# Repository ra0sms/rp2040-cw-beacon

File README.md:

# Beacon — CW (Morse) Beacon for HF or VHF Radio

A Morse-code beacon controller built around the [Waveshare RP2040-Zero](https://www.waveshare.com/wiki/RP2040-Zero) module (Raspberry Pi RP2040), designed for keying an HF/VHF FM/SSB/CW transmitter.

The project consists of:

- **Firmware** — generates a sine audio tone, controls the transmitter PTT and CW key, transmits a configurable message stored in flash and repeats it with a configurable pause. All parameters are configurable at runtime over a USB serial console and persist across power cycles.
- **Controller board** (KiCad) — power supply 8–15 V, audio output with attenuator and low-pass filter, open-collector PTT and CW key outputs, supply voltage divider and expansion headers. Gerber files are ready for ordering.
- **Desktop GUI** — configuration and monitoring tool for Linux and Windows.

## Repository layout

| Path | Contents |
|------|----------|
| [`code/Beacon/`](code/Beacon/) | Firmware source (Pico SDK, CMake) |
| [`firmware/`](firmware/) | Prebuilt firmware `.uf2` |
| [`gui/`](gui/) | Configuration GUI (`beacon_gui.py`, Windows build in `beacon_gui.zip`) |
| [`KiCad/beacon_rp2040/`](KiCad/beacon_rp2040/) | Board schematic and PCB (KiCad 10), schematic PDF, Gerber files, interactive BOM |
| [`scripts/`](scripts/) | Build / flash helper scripts |
| [`pics/`](pics/) | Schematic, 3D view, screenshots |

## Features

- **Telegraph tone output** — clean sine wave (DDS over a 62.5 kHz PWM carrier) with 5 ms raised-cosine rise/fall to avoid key clicks, 100–5000 Hz (600/800 Hz typical for FM audio), default **800 Hz**
- **PTT control** — asserted at the start of the transmission and released after the end of the message, with lead/tail delays
- **Morse message** — full A–Z, 0–9, `. , ? / - = @ : + ( ) " ' !` and prosigns (`<SK>`, `<BT>`, `<AR>`, …) encoding with standard element timing; speed set directly in WPM (default **20 WPM**)
- **Tone sequences** — an arbitrary chain of tone bursts ("freq:ms" pairs, `0` = silence), transmittable instead of (or after) the Morse message
- **Transmission modes** — `cw` (Morse only), `tones` (tone sequence only), or `both` (Morse, then tones) within one PTT
- **Non-volatile configuration** — stored in the last sector of the onboard flash; survives power-off and reflashing
- **Ready-to-flash firmware** — a prebuilt `.uf2` binary is included in [`firmware/`](firmware/), no toolchain required
- **USB console** — live configuration over the USB CDC serial port
- **Transmitter safety** — time-out timer (PTT is forcibly released after 120 s), hardware watchdog (reboot with PTT off if the firmware hangs), `txen 0` aborts the transmission immediately
- **Accurate keying** — the whole transmission is laid out in advance and played by a hardware timer, so console activity and USB output do not affect the timing
- **Status LED** — onboard WS2812 (GP16): steady green in the pause, red blinking in sync with the keying during transmission; brightness configurable

## Hardware

### Controller board

Two-layer board, 75 × 32 mm, four M3 mounting holes (connected to GND). The RP2040-Zero module is soldered flat onto the board by its castellated pads; its USB-C connector faces the board edge and is used for configuration and firmware updates. Full schematic: [`beacon_rp2040.pdf`](KiCad/beacon_rp2040/beacon_rp2040.pdf).

#### Main connector J1 (to the transmitter)

| Pin | Label | Function |
|-----|-------|----------|
| 1 | `8-15V` | Supply input, 8–15 V DC (reverse-polarity protected) |
| 2 | `GND` | Ground |
| 3 | `AUDIO` | Audio output → transmitter microphone / modulation input |
| 4 | `CW_OUT` | CW key output, open collector to GND (closed while the tone sounds) |
| 5 | `PTT_OUT` | PTT output, open collector to GND (closed during transmission) |
| 6 | `GND` | Ground |

#### Outputs

- **PTT / CW key** — BC817 NPN transistors, open collector to ground: connect directly to the radio's PTT and straight-key inputs (both are normally "close to ground" lines). Up to 45 V and ~50–100 mA. When switching a relay coil, put a flyback diode across the coil. Each output has a 100 nF capacitor to ground against RF pickup and a 10 kΩ pull-down on the base drive, so the outputs stay off while the module boots.
- **Audio** — GP15 sine → 34 kΩ / 1 kΩ divider → 47 nF low-pass (≈3.5 kHz, suppresses the 62.5 kHz PWM carrier) → 10 µF coupling capacitor. Output level is about 90 mV p-p (≈30 mV RMS) at the default settings — suitable for a microphone input. For a line/data input increase the 1 kΩ resistor (R2) or decrease the 34 kΩ resistor (R1).
- **Status LEDs** — headers `LED` / `CW`–`GND` and `LED` / `PTT`–`GND` for external indicator LEDs (anode to `CW`/`PTT`, cathode to `GND`; 1 kΩ series resistors are on the board). They light while the key is closed / PTT is active. The onboard WS2812 of the RP2040-Zero shows the beacon state as well.

#### Power supply

- Input 8–15 V → MBR0540 reverse-polarity diode → LM7805 (TO-220) → MBR0540 → +5 V rail → RP2040-Zero (its own 3.3 V regulator).
- The output diode isolates the regulator from USB: with only USB connected the board is powered from the computer (handy for configuration); with both connected the higher voltage wins, nothing is back-fed.
- The 7805 needs ~2 V of headroom plus ~0.3 V for the input diode, hence the 8 V minimum. At 13.8 V it dissipates about 8.5 V × load current — fine for the beacon itself (tens of mA) without a heatsink; keep external loads on the 5 V / 3.3 V headers small (≲100 mA) or add a heatsink.
- Supply voltage divider 100 kΩ / 10 kΩ + 100 nF to **GP26 (ADC0)**, ratio 1:11, range up to ~36 V — reserved for supply monitoring (not used by the firmware yet).

#### Expansion headers

| Header | Pins |
|--------|------|
| J2 `GPIOs` (18 pins) | 1 `3.3V`, 2–8 `GP0`–`GP6`, 9–14 `GP8`–`GP13`, 15–17 `GP27`–`GP29` (ADC1–ADC3), 18 `GND` |
| J3 `GND` | 3 × GND |
| J4 `5V` | 3 × +5 V rail (≈4.7 V after the isolation diode, or USB 5 V) |

GPIOs are 3.3 V logic and are not 5 V tolerant. GP7, GP14, GP15 and GP26 are used by the board and are not brought out.

#### RP2040-Zero pin usage

| Signal | GPIO | Description |
|--------|------|-------------|
| Tone   | GP15 | Audio tone (sine via PWM) → J1 `AUDIO` |
| PTT    | GP14 | PTT transistor → J1 `PTT_OUT`, PTT LED |
| CW key | GP7  | CW key transistor → J1 `CW_OUT`, CW LED |
| Vin sense | GP26 | Supply voltage divider (ADC0) |
| WS2812 | GP16 | Onboard status LED (built into the module) |

#### Manufacturing files

| File | Contents |
|------|----------|
| [`KiCad/beacon_rp2040/beacon_rp2040_gerbers.zip`](KiCad/beacon_rp2040/beacon_rp2040_gerbers.zip) | Gerber + drill files, ready to upload to a PCB manufacturer (2 layers, 1.6 mm) |
| [`KiCad/beacon_rp2040/gerbers/`](KiCad/beacon_rp2040/gerbers/) | The same files, unpacked |
| [`KiCad/beacon_rp2040/bom/ibom.html`](KiCad/beacon_rp2040/bom/ibom.html) | Interactive BOM / placement helper (download and open in a browser) |
| [`KiCad/beacon_rp2040/beacon_rp2040.pdf`](KiCad/beacon_rp2040/beacon_rp2040.pdf) | Schematic (PDF) |

#### Bill of materials

| Qty | Value | Package | References |
|-----|-------|---------|------------|
| 1 | Waveshare RP2040-Zero | castellated module | U1 |
| 1 | LM7805 | TO-220 | U2 |
| 2 | BC817 (2N7002 also fits) | SOT-23 | Q3, Q4 |
| 2 | MBR0540 | SOD-123 | D1, D4 |
| 1 | 34 kΩ (33 kΩ is fine) | 1206 | R1 |
| 1 | 100 kΩ | 1206 | R7 |
| 3 | 10 kΩ | 1206 | R3, R5, R8 |
| 5 | 1 kΩ | 1206 | R2, R4, R6, R9, R10 |
| 5 | 100 nF | 1206 | C2, C3, C5, C10, C11 |
| 3 | 10 µF ceramic, ≥25 V | 1206 | C4, C9, C12 |
| 1 | 47 nF | 1206 | C6 |
| 2 | 47 µF electrolytic, ≥25 V | radial 5 mm | C13, C14 |
| 1 | Pin header 1×6, 2.54 mm | THT | J1 |
| 1 | Pin header 1×18, 2.54 mm | THT | J2 |
| 2 | Pin header 1×3, 2.54 mm | THT | J3, J4 |
| 2 | Pin header 1×2, 2.54 mm (external LEDs) | THT | D2, D3 |

## Flashing

A prebuilt firmware binary is included in the repository: [`firmware/Beacon-v0.2.uf2`](firmware/Beacon-v0.2.uf2). You do not need to build anything to flash it.

**Method 1 — BOOTSEL button:**

1. Hold the BOOT button and connect the board via USB.
2. The board appears as a USB mass-storage device (`RPI-RP2`).
3. Copy the firmware: `cp firmware/Beacon-v0.2.uf2 /run/media/$USER/RPI-RP2/`

**Method 2 — picotool (no button required):**

```bash
picotool load firmware/Beacon-v0.2.uf2 -fx
```

If the currently running firmware does not support USB reboot, use the BOOTSEL button method.

## Configuration commands (USB console)

Connect to the board's serial port (`/dev/ttyACM0` on Linux, e.g. `minicom -D /dev/ttyACM0` or `picocom /dev/ttyACM0`). Any baud rate works.

Type the command and press **Enter**. If your terminal can send no line ending, the line is executed automatically after a 5-second pause in typing.

| Command        | Description                                        |
|----------------|----------------------------------------------------|
| `msg <text>`   | Set message text (A–Z, 0–9, `. , ? / - = @ : + ( ) " ' !`); prosigns in angle brackets are sent without letter gaps, e.g. `<SK>`, `<BT>`. Max 95 characters |
| `tone <hz>`    | Set tone frequency, 100–5000 Hz                    |
| `pause <sec>`  | Pause between message repeats, 0–3600 s            |
| `wpm <5..60>`  | Keying speed, words per minute (dot = 1200 / wpm)  |
| `tones <f:d> ...` | Tone sequence: `freq:ms` pairs, freq 0–5000 Hz (`0` = silence), duration 10–10000 ms, up to 24 entries. Without arguments — show current sequence |
| `txmode cw\|tones\|both` | What to transmit: Morse only / tone sequence only / both |
| `txen <0\|1>`   | Enable/disable transmission (0 = stops immediately, PTT released; beacon stays silent, e.g. while tuning) |
| `led <0..100>` | Status LED brightness, % (default 20)              |
| `save`         | Write current configuration to flash (during a transmission it is deferred until the transmission ends) |
| `show`         | Print current configuration                        |
| `default`      | Restore factory defaults                           |
| `ver`          | Firmware version (program version and git revision) |
| `help`         | Show command list                                  |

Changes take effect immediately (from the next transmission); use `save` to make them permanent. Invalid values are rejected with an `error:`/`usage:` reply and leave the setting unchanged. When the message, speed, mode or tone sequence makes a transmission longer than the 120 s time-out, a `warning:` is printed — such a transmission would be cut off. `show` also prints the transmission length (`txlen`).

The configuration is stored with a version number and CRC-32; a configuration saved by firmware v0.1 is migrated automatically on first boot.

### Example session

```
msg CQ CQ CQ DE RA0SMS K
tone 600
pause 15
wpm 18
txmode both
tones 800:150 0:100 800:150 0:100 1200:150 0:500
save
```

## Helper scripts

| Script | Purpose |
|--------|---------|
| [`scripts/build.sh`](scripts/build.sh) | Configure (once) and build the firmware → `code/Beacon/build/Beacon.uf2` |
| [`scripts/flash.sh`](scripts/flash.sh) | Flash the built firmware to the board via picotool (auto-detects the picotool from the Pico VS Code extension; override with `PICOTOOL=/path/to/picotool`) |
| [`scripts/build_gui_exe.bat`](scripts/build_gui_exe.bat) | (Windows) Build the standalone `gui/beacon_gui.exe` with PyInstaller (pack it into `gui/beacon_gui.zip` for the repository) |
| [`scripts/update_firmware.sh`](scripts/update_firmware.sh) | Copy the freshly built binary to the tracked [`firmware/Beacon-v0.2.uf2`](firmware/Beacon-v0.2.uf2) |

Typical workflow: `./scripts/build.sh && ./scripts/flash.sh`, then `./scripts/update_firmware.sh` before committing a new firmware version.

## Building from source

If you want to modify the firmware, build it yourself. The project uses:

- **[Raspberry Pi Pico SDK](https://github.com/raspberrypi/pico-sdk)** 2.3.1 (developed with this version; other 2.x versions likely work)
- **CMake** ≥ 3.13
- **ARM GCC cross-toolchain** — `arm-none-eabi-gcc` (the SDK 2.x toolchain package `15_2_Rel1` or any recent version)
- **Ninja** or GNU Make (Ninja is recommended)

### Installing the toolchain

**Fedora / RHEL:**

```bash
sudo dnf install arm-none-eabi-gcc-cs arm-none-eabi-newlib cmake ninja-build
git clone -b 2.3.1 https://github.com/raspberrypi/pico-sdk.git ~/pico-sdk
export PICO_SDK_PATH=~/pico-sdk   # add to ~/.bashrc or ~/.zshrc
```

**Debian / Ubuntu:**

```bash
sudo apt install gcc-arm-none-eabi libnewlib-arm-none-eabi libstdc++-arm-none-eabi-newlib cmake ninja-build
git clone -b 2.3.1 https://github.com/raspberrypi/pico-sdk.git ~/pico-sdk
export PICO_SDK_PATH=~/pico-sdk   # add to ~/.bashrc
```

Alternatively, install the official **Raspberry Pi Pico VS Code extension** — it manages the SDK, toolchain, ninja and picotool automatically (in `~/.pico-sdk`); the project's VS Code configuration in [`code/Beacon/.vscode/`](code/Beacon/.vscode/) is prepared for it.

### Building

```bash
cmake -B code/Beacon/build -S code/Beacon
cmake --build code/Beacon/build
```

The firmware binary is produced at `code/Beacon/build/Beacon.uf2`.

`picotool` (for USB flashing without the BOOTSEL button) is bundled with the VS Code extension, or can be built from [picotool](https://github.com/raspberrypi/picotool) / installed as `picotool` package on recent distros. Without it, use the BOOTSEL button method.

### Flashing the built firmware

**Method 1 — BOOTSEL button:**

1. Hold the BOOT button and connect the board via USB.
2. The board appears as a USB mass-storage device (`RPI-RP2`).
3. Copy the firmware: `cp code/Beacon/build/Beacon.uf2 /run/media/$USER/RPI-RP2/`

**Method 2 — picotool (no button required):**

```bash
picotool load code/Beacon/build/Beacon.uf2 -fx
```

If the currently running firmware does not support USB reboot, use the BOOTSEL button method.

## GUI (configuration tool)

A PyQt5/PyQt6 desktop GUI is available for convenient configuration and monitoring: [`gui/beacon_gui.py`](gui/beacon_gui.py).

**Windows users:** a standalone build that needs no Python installation is available: [`gui/beacon_gui.zip`](gui/beacon_gui.zip) — download, unpack and run `beacon_gui.exe`. On first launch the SmartScreen may warn about an unsigned binary; choose "More info" → "Run anyway".

Install the Python dependencies:

```bash
pip install -r requirements.txt
```

This installs **pyserial** and **PyQt5**. If only **PyQt6** is available (or PyQt5 is not installed), the GUI automatically uses PyQt6 instead — pyserial is required in either case.

Run the GUI:

```bash
python3 gui/beacon_gui.py
```

Features:

- Serial port selection with auto-detection of the Pico CDC port, connect/disconnect
- Editing all parameters: message, CW tone, keying speed (WPM), tone sequence, TX mode, pause, LED brightness; the message field only accepts characters the firmware can send
- **Apply** sends the fields one by one, waiting for the device's reply to each; rejected values and time-out warnings are reported in a summary dialog
- **Save to flash** — Apply, then `save`; **Read from device** — fills the fields from the device; **Defaults**
- **Transmission enabled** checkbox — temporarily stop the beacon (e.g. while tuning) and resume it later
- Firmware version display; a lost connection (cable unplugged, board reset) is detected automatically
- Live device log, optional hiding of TX monitor output
- Manual command line for any console command

On connection the GUI automatically requests the current configuration from the device and fills in the fields.

## Pin configuration

Pins and fixed parameters are defined at the top of [`code/Beacon/Beacon.c`](code/Beacon/Beacon.c):

```c
#define TONE_PIN          15   // Telegraph tone output
#define PTT_PIN           14   // PTT output (active high)
#define KEY_PIN           7    // CW key output (active high)
#define PTT_LEAD_MS       1000 // PTT lead-in delay, ms
#define PTT_TAIL_MS       100  // PTT tail delay, ms
#define TX_MAX_MS         120000 // Time-out timer: max PTT time per transmission, ms
#define WATCHDOG_MS       3000 // Watchdog timeout, ms
```

The PTT and CW key GPIOs are always **active high** (logic 1 while transmitting / keyed) — this is fixed in the firmware, no configuration needed. On the controller board they drive the open-collector transistors, so J1 `PTT_OUT` / `CW_OUT` are closed to ground while active.

## License

MIT

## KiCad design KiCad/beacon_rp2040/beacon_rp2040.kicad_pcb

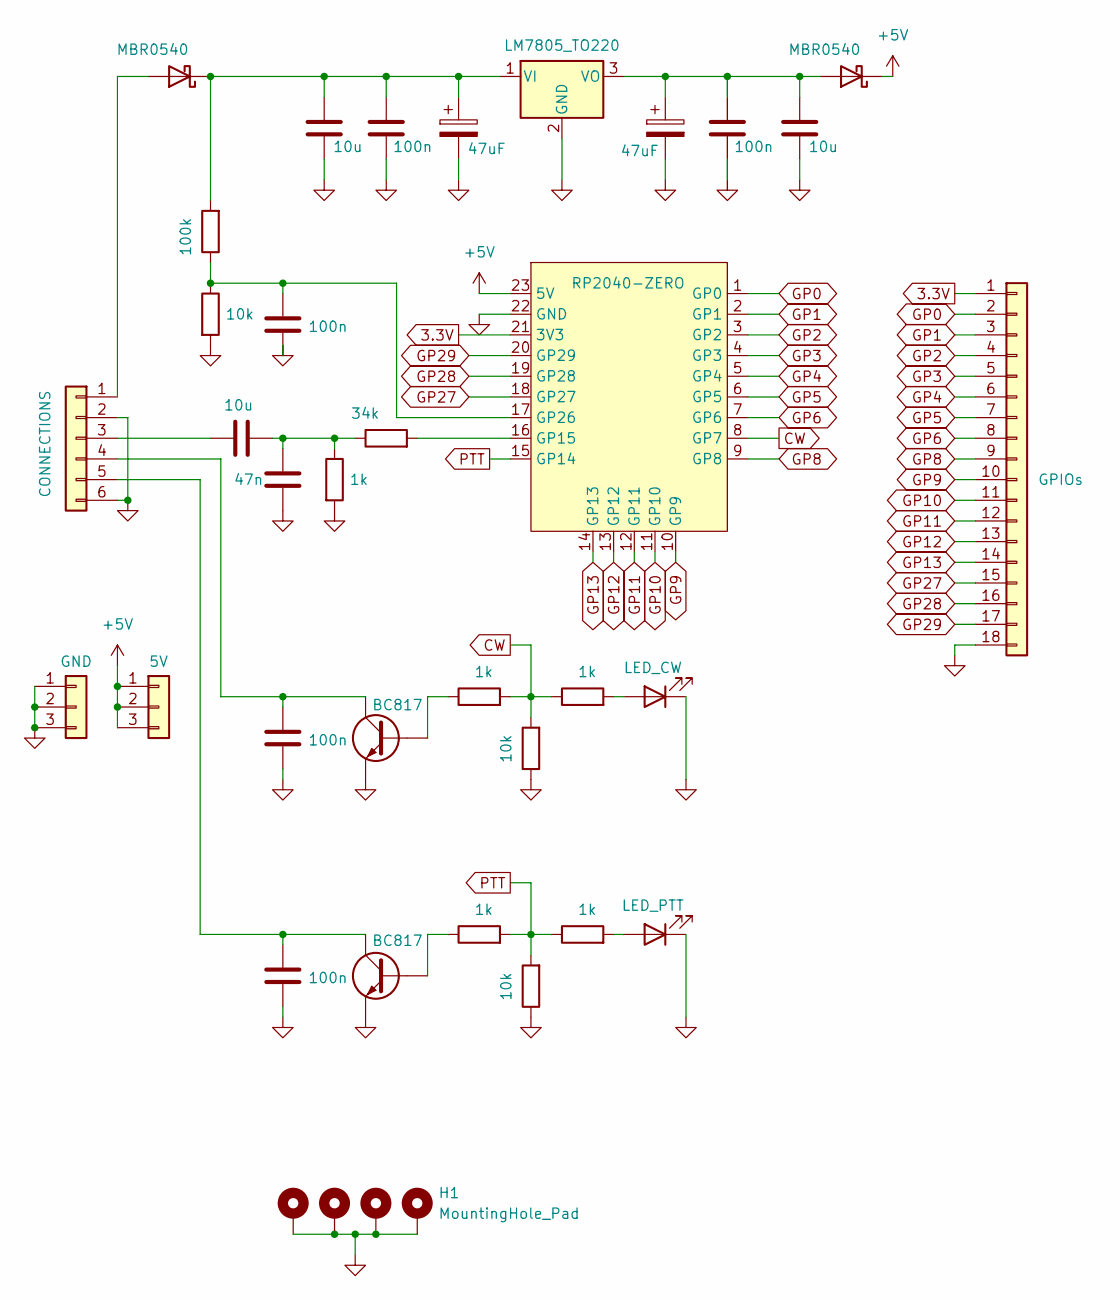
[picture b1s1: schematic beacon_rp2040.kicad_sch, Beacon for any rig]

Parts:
C2, C3, C5, C10, C11: 100n; C_1206_3216Metric
C4, C9, C12: 10u; C_1206_3216Metric
C6: 47n; C_1206_3216Metric
C13, C14: 47uF; CP_Radial_D5.0mm_P2.50mm
D1, D4: MBR0540; D_SOD-123
D2: LED_CW; PinHeader_1x02_P2.54mm_Vertical
D3: LED_PTT; PinHeader_1x02_P2.54mm_Vertical
H1, H2, H3, H4: MountingHole_Pad; MountingHole_3.2mm_M3_DIN965_Pad
J1: CONNECTIONS; PinHeader_1x06_P2.54mm_Vertical
J2: GPIOs; PinHeader_1x18_P2.54mm_Vertical
J3: GND; PinHeader_1x03_P2.54mm_Vertical
J4: 5V; PinHeader_1x03_P2.54mm_Vertical
Q3, Q4: BC817; SOT-23-3
R1: 34k; R_1206_3216Metric
R2, R4, R6, R9, R10: 1k; R_1206_3216Metric
R3, R5, R8: 10k; R_1206_3216Metric
R7: 100k; R_1206_3216Metric
U1: RP2040-ZERO; COMM-SMD_RP2040-ZERO; MPN RP2040-Zero; LCSC Part C5350143
U2: LM7805_TO220; TO-220-3_Vertical

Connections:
3.3V: J2.1, U1.21 (3V3)
+5V: D1.1 (K), J4.1, J4.2, J4.3, U1.23 (5V)
CW: R3.2, R4.1, R9.2, U1.8 (GP7)
GND: C2.1, C3.1, C5.1, C6.1, C9.2, C10.2, C11.2, C12.2, C13.2, C14.2, D2.1 (K), D3.1 (K), H1.1 (1_1), H2.1 (1_1), H3.1 (1_1), H4.1 (1_1), J1.2, J1.6, J2.18, J3.1, J3.2, J3.3, Q3.2 (E), Q4.2 (E), R2.2, R3.1, R5.1, R8.2, U1.22 (GND), U2.2 (GND)
GP0: J2.2, U1.1 (GP0)
GP1: J2.3, U1.2 (GP1)
GP2: J2.4, U1.3 (GP2)
GP3: J2.5, U1.4 (GP3)
GP4: J2.6, U1.5 (GP4)
GP5: J2.7, U1.6 (GP5)
GP6: J2.8, U1.7 (GP6)
GP8: J2.9, U1.9 (GP8)
GP9: J2.10, U1.10 (GP9)
GP10: J2.11, U1.11 (GP10)
GP11: J2.12, U1.12 (GP11)
GP12: J2.13, U1.13 (GP12)
GP13: J2.14, U1.14 (GP13)
GP27: J2.15, U1.18 (GP27)
GP28: J2.16, U1.19 (GP28)
GP29: J2.17, U1.20 (GP29)
unnamed: C4.1, C6.2, R1.1, R2.1
unnamed: C11.1, C12.1, C13.1, D1.2 (A), U2.3 (VO)
unnamed: D2.2 (A), R4.2
unnamed: D3.2 (A), R6.2
unnamed: D4.2 (A), J1.1
unnamed: C9.1, C10.1, C14.1, D4.1 (K), R7.2, U2.1 (VI)
unnamed: C4.2, J1.3
unnamed: C2.2, J1.4, Q4.3 (C)
unnamed: C3.2, J1.5, Q3.3 (C)
unnamed: Q3.1 (B), R10.1
unnamed: Q4.1 (B), R9.1
unnamed: R1.2, U1.16 (GP15)
unnamed: C5.2, R7.1, R8.1, U1.17 (GP26)
PTT: R5.2, R6.1, R10.2, U1.15 (GP14)

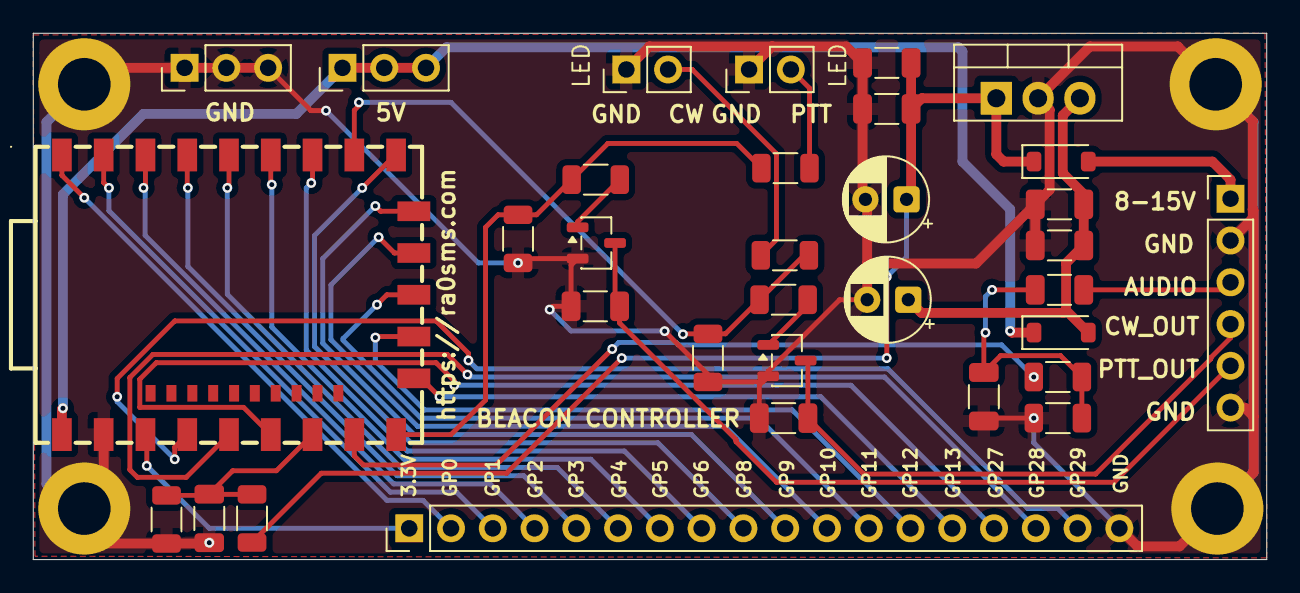
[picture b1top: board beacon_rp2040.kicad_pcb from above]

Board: 2 copper layers, 75.0 x 32.0 mm, 37 parts (0 on the bottom side), 34 nets.
